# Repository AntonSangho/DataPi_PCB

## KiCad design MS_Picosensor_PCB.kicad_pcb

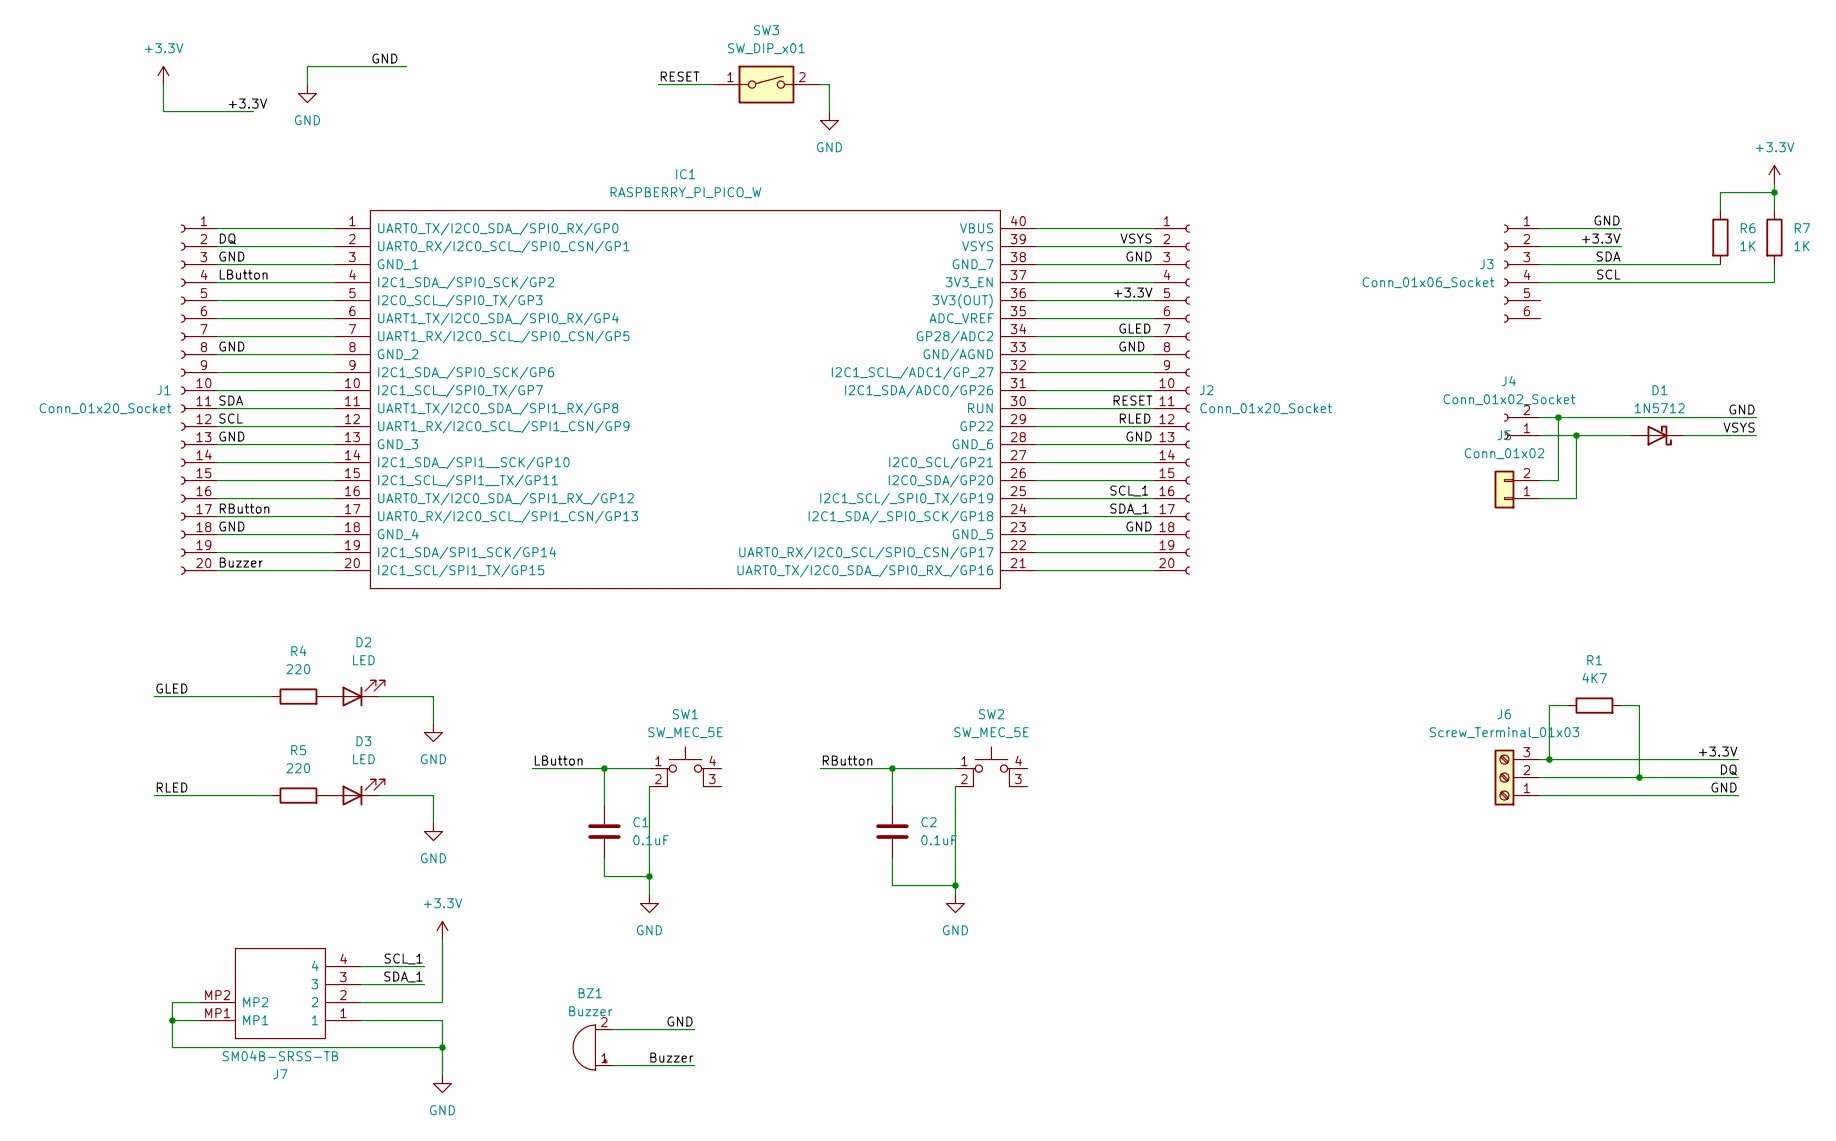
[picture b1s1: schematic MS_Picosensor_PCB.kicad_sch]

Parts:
BZ1: Buzzer; Buzzer_12x9.5RM7.6
C1, C2: 0.1uF; C_Disc_D3.0mm_W1.6mm_P2.50mm
D1: 1N5712; D_DO-35_SOD27_P7.62mm_Horizontal
D2, D3: LED; LED_D3.0mm
IC1: RASPBERRY_PI_PICO_W; RASPBERRYPIPICOW; Manufacturer_Part_Number RASPBERRY PI PICO W
J1, J2: Conn_01x20_Socket; PinSocket_1x20_P2.54mm_Vertical
J3: Conn_01x06_Socket; PinSocket_1x06_P2.54mm_Horizontal
J4: Conn_01x02_Socket; JST_PH_B2B-PH-K_1x02_P2.00mm_Vertical
J5: Conn_01x02; PinHeader_1x02_P1.27mm_Vertical
J6: Screw_Terminal_01x03; TerminalBlock_4Ucon_1x03_P3.50mm_Horizontal
J7: SM04B-SRSS-TB; SM04BSRSSTB; Manufacturer_Part_Number SM04B-SRSS-TB
R1: 4K7; R_Axial_DIN0207_L6.3mm_D2.5mm_P10.16mm_Horizontal
R4, R5: 220; R_Axial_DIN0207_L6.3mm_D2.5mm_P10.16mm_Horizontal
R6, R7: 1K; R_Axial_DIN0207_L6.3mm_D2.5mm_P10.16mm_Horizontal
SW1, SW2: SW_MEC_5E; SW_TH_Tactile_Omron_B3F-10xx
SW3: SW_DIP_x01; SW_PUSH_1P1T_6x3.5mm_H4.3_APEM_MJTP1243

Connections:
+3.3V: IC1.36 (3V3(OUT)), J2.5, J3.2, J6.3, J7.2, R1.1, R6.1, R7.1
/Buzzer: BZ1.1 (-), IC1.20 (I2C1_SCL/SPI1_TX/GP15), J1.20
/DQ: IC1.2 (UART0_RX/I2C0_SCL_/SPI0_CSN/GP1), J1.2, J6.2, R1.2
/GLED: IC1.34 (GP28/ADC2), J2.7, R4.1
/LButton: C1.1, IC1.4 (I2C1_SDA_/SPI0_SCK/GP2), J1.4, SW1.1
/RButton: C2.1, IC1.17 (UART0_RX/I2C0_SCL_/SPI1_CSN/GP13), J1.17, SW2.1
/RESET: IC1.30 (RUN), J2.11, SW3.1
/RLED: IC1.29 (GP22), J2.12, R5.1
/SCL: IC1.12 (UART1_RX/I2C0_SCL_/SPI1_CSN/GP9), J1.12, J3.4, R7.2
/SCL_1: IC1.25 (I2C1_SCL/_SPI0_TX/GP19), J2.16, J7.4
/SDA: IC1.11 (UART1_TX/I2C0_SDA_/SPI1_RX/GP8), J1.11, J3.3, R6.2
/SDA_1: IC1.24 (I2C1_SDA/_SPI0_SCK/GP18), J2.17, J7.3
/VSYS: D1.1 (K), IC1.39 (VSYS), J2.2
GND: BZ1.2 (+), C1.2, C2.2, D2.1 (K), D3.1 (K), IC1.3 (GND_1), IC1.8 (GND_2), IC1.13 (GND_3), IC1.18 (GND_4), IC1.23 (GND_5), IC1.28 (GND_6), IC1.33 (GND/AGND), IC1.38 (GND_7), J1.3, J1.8, J1.13, J1.18, J2.3, J2.8, J2.13, J2.18, J3.1, J4.2, J5.2, J6.1, J7.1, J7.MP1, J7.MP2, SW1.2, SW2.2, SW3.2
unnamed: D1.2 (A), J4.1, J5.1
unnamed: D2.2 (A), R4.2
unnamed: D3.2 (A), R5.2
unnamed: IC1.1 (UART0_TX/I2C0_SDA_/SPI0_RX/GP0), J1.1
unnamed: IC1.5 (I2C0_SCL_/SPI0_TX/GP3), J1.5
unnamed: IC1.6 (UART1_TX/I2C0_SDA_/SPI0_RX/GP4), J1.6
unnamed: IC1.7 (UART1_RX/I2C0_SCL_/SPI0_CSN/GP5), J1.7
unnamed: IC1.9 (I2C1_SDA_/SPI0_SCK/GP6), J1.9
unnamed: IC1.10 (I2C1_SCL_/SPI0_TX/GP7), J1.10
unnamed: IC1.14 (I2C1_SDA_/SPI1__SCK/GP10), J1.14
unnamed: IC1.15 (I2C1_SCL_/SPI1__TX/GP11), J1.15
unnamed: IC1.16 (UART0_TX/I2C0_SDA_/SPI1_RX_/GP12), J1.16
unnamed: IC1.19 (I2C1_SDA/SPI1_SCK/GP14), J1.19
unnamed: IC1.40 (VBUS), J2.1
unnamed: IC1.37 (3V3_EN), J2.4
unnamed: IC1.35 (ADC_VREF), J2.6
unnamed: IC1.32 (I2C1_SCL_/ADC1/GP_27), J2.9
unnamed: IC1.31 (I2C1_SDA/ADC0/GP26), J2.10
unnamed: IC1.27 (I2C0_SCL/GP21), J2.14
unnamed: IC1.26 (I2C0_SDA/GP20), J2.15
unnamed: IC1.22 (UART0_RX/I2C0_SCL/SPIO_CSN/GP17), J2.19
unnamed: IC1.21 (UART0_TX/I2C0_SDA_/SPI0_RX_/GP16), J2.20

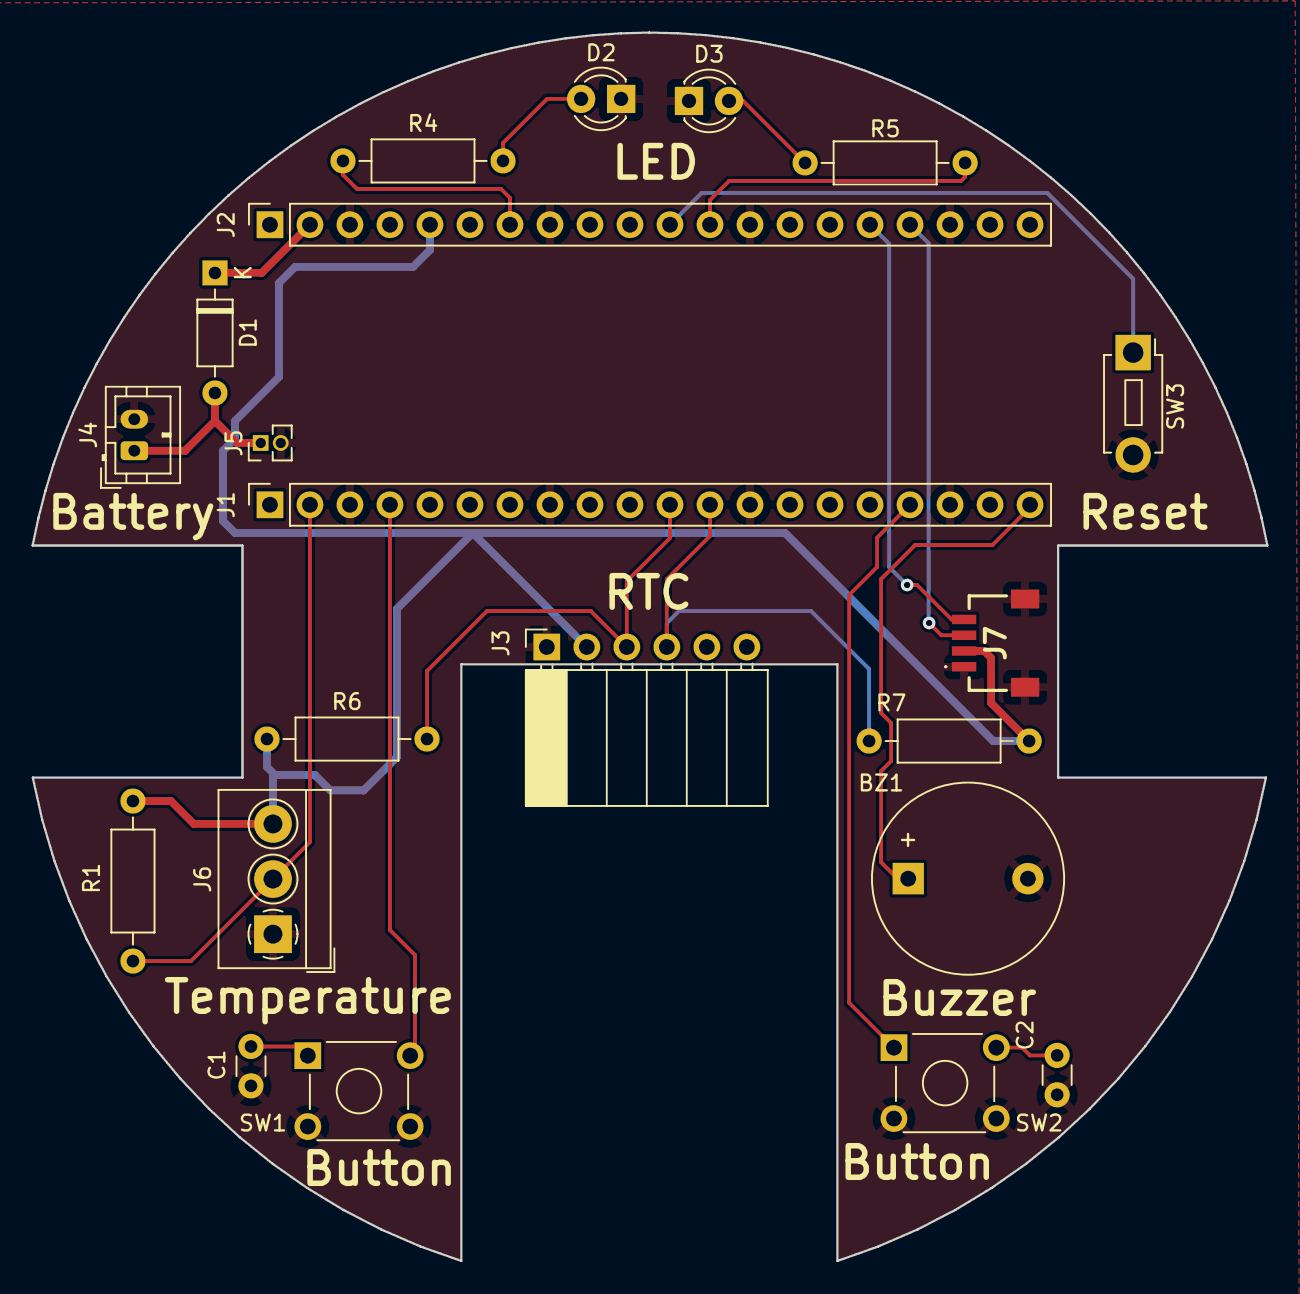
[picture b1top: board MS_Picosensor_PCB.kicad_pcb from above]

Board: 2 copper layers, 78.4 x 78.0 mm, 21 parts (0 on the bottom side), 17 nets.

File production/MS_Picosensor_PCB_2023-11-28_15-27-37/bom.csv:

Designator,Footprint,Quantity,Value,LCSC Part #
BZ1,Buzzer_12x9.5RM7.6,1,Buzzer,
"J1, J2",PinSocket_1x20_P2.54mm_Vertical,2,Conn_01x20_Socket,
J3,PinSocket_1x04_P2.54mm_Horizontal,1,Conn_01x06_Socket,
J4,JST_PH_B2B-PH-K_1x02_P2.00mm_Vertical,1,Conn_01x02_Socket,
J5,PinHeader_1x02_P1.27mm_Vertical,1,Conn_01x02,
J6,TerminalBlock_4Ucon_1x03_P3.50mm_Horizontal,1,Screw_Terminal_01x03,
JP1,SolderJumper-2_P1.3mm_Open_RoundedPad1.0x1.5mm,1,Jumper_2_Open,
R1,R_Axial_DIN0207_L6.3mm_D2.5mm_P10.16mm_Horizontal,1,4K7,
"SW1, SW2",SW_TH_Tactile_Omron_B3F-10xx,2,SW_MEC_5E,

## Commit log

2023-11-30 First commit.
2023-11-30 change in schematic
2023-11-30 change location of buzzer
2023-11-30 change in schematic 2
2023-12-19 3v3 output
2023-12-19 add part for smd
